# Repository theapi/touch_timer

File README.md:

# touch_timer
Kitchen timer with a touch interface

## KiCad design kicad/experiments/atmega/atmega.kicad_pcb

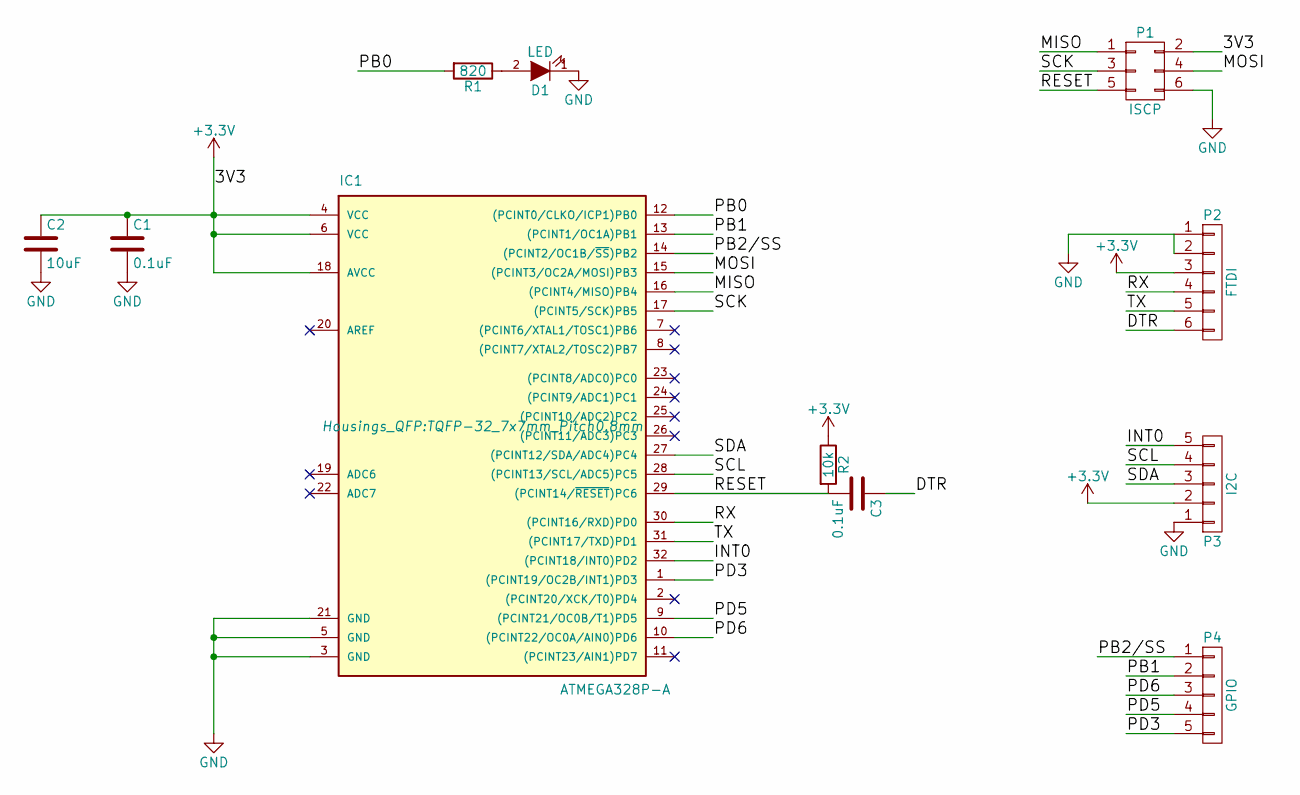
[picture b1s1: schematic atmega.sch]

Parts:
C1, C3: 0.1uF; C_0805_HandSoldering
C2: 10uF; C_0805_HandSoldering
D1: LED; LED_0805
IC1: ATMEGA328P-A; TQFP-32_7x7mm_Pitch0.8mm
P1: ISCP; Socket_Strip_Straight_2x03
P2: FTDI; Socket_Strip_Straight_1x06
P3: I2C; Pin_Header_Straight_1x05
P4: GPIO; Pin_Header_Straight_1x05
R1: 820; R_0805_HandSoldering
R2: 10k; R_0805_HandSoldering

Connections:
+3V3: C1.1, C2.1, IC1.4 (VCC), IC1.6 (VCC), IC1.18 (AVCC), P1.2, P2.3, P3.2, R2.1
/DTR: C3.1, P2.6
/INT0: IC1.32 ((PCINT18/INT0)PD2), P3.5
/MISO: IC1.16 ((PCINT4/MISO)PB4), P1.1
/MOSI: IC1.15 ((PCINT3/OC2A/MOSI)PB3), P1.4
/PB0: IC1.12 ((PCINT0/CLKO/ICP1)PB0), R1.2
/PB1: IC1.13 ((PCINT1/OC1A)PB1), P4.2
/PB2/SS: IC1.14 ((PCINT2/OC1B/~SS~)PB2), P4.1
/PD3: IC1.1 ((PCINT19/OC2B/INT1)PD3), P4.5
/PD5: IC1.9 ((PCINT21/OC0B/T1)PD5), P4.4
/PD6: IC1.10 ((PCINT22/OC0A/AIN0)PD6), P4.3
/RESET: C3.2, IC1.29 ((PCINT14/~RESET~)PC6), P1.5, R2.2
/RX: IC1.30 ((PCINT16/RXD)PD0), P2.4
/SCK: IC1.17 ((PCINT5/SCK)PB5), P1.3
/SCL: IC1.28 ((PCINT13/SCL/ADC5)PC5), P3.4
/SDA: IC1.27 ((PCINT12/SDA/ADC4)PC4), P3.3
/TX: IC1.31 ((PCINT17/TXD)PD1), P2.5
GND: C1.2, C2.2, D1.1 (K), IC1.3 (GND), IC1.5 (GND), IC1.21 (GND), P1.6, P2.1, P2.2, P3.1
unnamed: D1.2 (A), R1.1

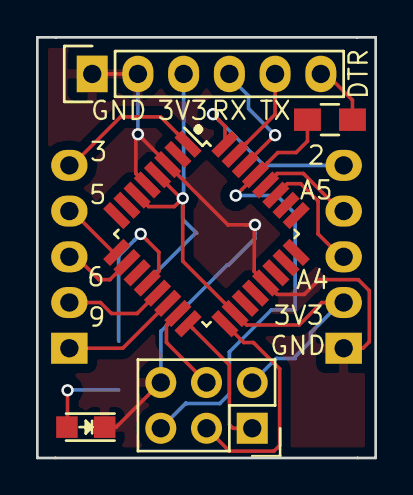
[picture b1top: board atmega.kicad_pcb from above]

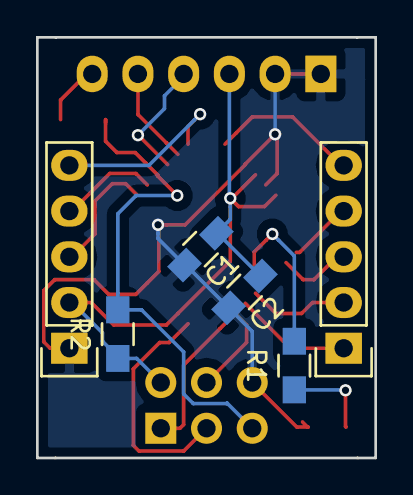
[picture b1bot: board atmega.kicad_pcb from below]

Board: 2 copper layers, 18.8 x 23.4 mm, 11 parts (6 on the bottom side), 19 nets.

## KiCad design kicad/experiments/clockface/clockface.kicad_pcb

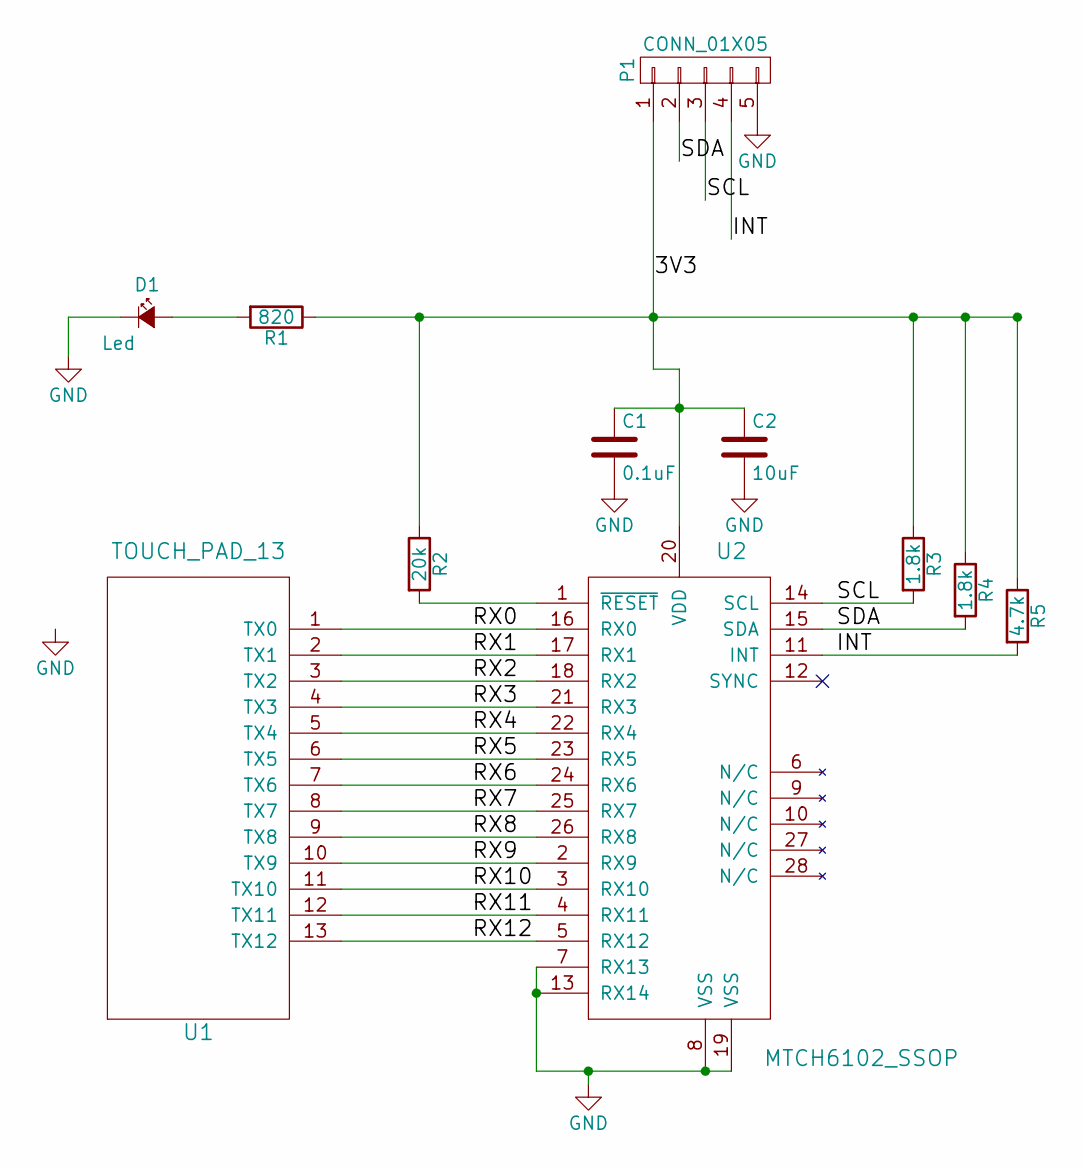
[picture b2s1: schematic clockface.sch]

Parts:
C1: 0.1uF; C_0805_HandSoldering
C2: 10uF; C_0805_HandSoldering
D1: Led; LED_0805
P1: CONN_01X05; SMD_Header_Straight_1x05
R1: 820; R_0805_HandSoldering
R2: 20k; R_0805_HandSoldering
R3, R4: 1.8k; R_0805_HandSoldering
R5: 4.7k; R_0805_HandSoldering
U1: TOUCH_PAD_13; CPA_12
U2: MTCH6102_SSOP; SSOP-28_5.3x10.2mm_Pitch0.65mm_masked

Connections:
/3V3: C1.1, C2.1, P1.1, R1.1, R2.1, R3.1, R4.1, R5.1, U2.20 (VDD)
/INT: P1.4, R5.2, U2.11 (INT)
/RX0: U1.1 (TX0), U2.16 (RX0)
/RX1: U1.2 (TX1), U2.17 (RX1)
/RX2: U1.3 (TX2), U2.18 (RX2)
/RX3: U1.4 (TX3), U2.21 (RX3)
/RX4: U1.5 (TX4), U2.22 (RX4)
/RX5: U1.6 (TX5), U2.23 (RX5)
/RX6: U1.7 (TX6), U2.24 (RX6)
/RX7: U1.8 (TX7), U2.25 (RX7)
/RX8: U1.9 (TX8), U2.26 (RX8)
/RX9: U1.10 (TX9), U2.2 (RX9)
/RX10: U1.11 (TX10), U2.3 (RX10)
/RX11: U1.12 (TX11), U2.4 (RX11)
/RX12: U1.13 (TX12), U2.5 (RX12)
/SCL: P1.3, R3.2, U2.14 (SCL)
/SDA: P1.2, R4.2, U2.15 (SDA)
GND: C1.2, C2.2, D1.1 (K), P1.5, U1.14, U2.7 (RX13), U2.8 (VSS), U2.13 (RX14), U2.19 (VSS)
unnamed: D1.2 (A), R1.2
unnamed: R2.2, U2.1 (~RESET)

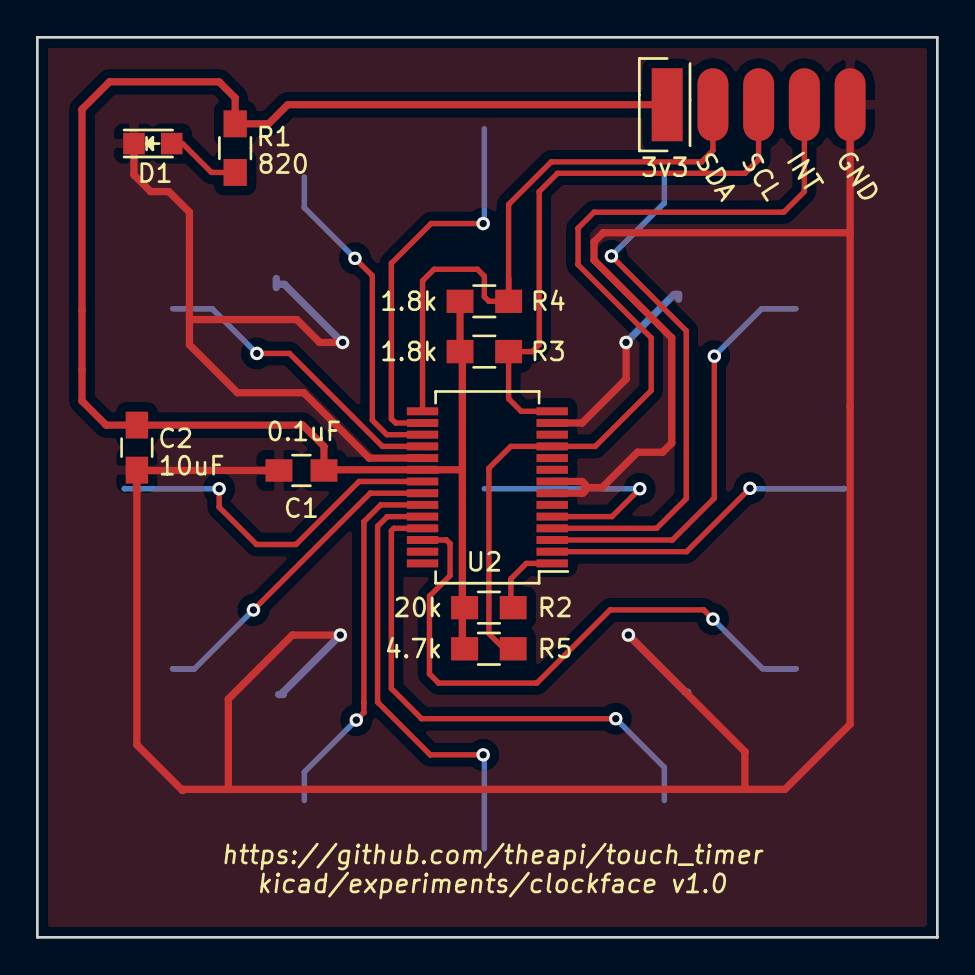
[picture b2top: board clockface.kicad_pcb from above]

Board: 2 copper layers, 50.0 x 50.0 mm, 11 parts (1 on the bottom side), 20 nets.

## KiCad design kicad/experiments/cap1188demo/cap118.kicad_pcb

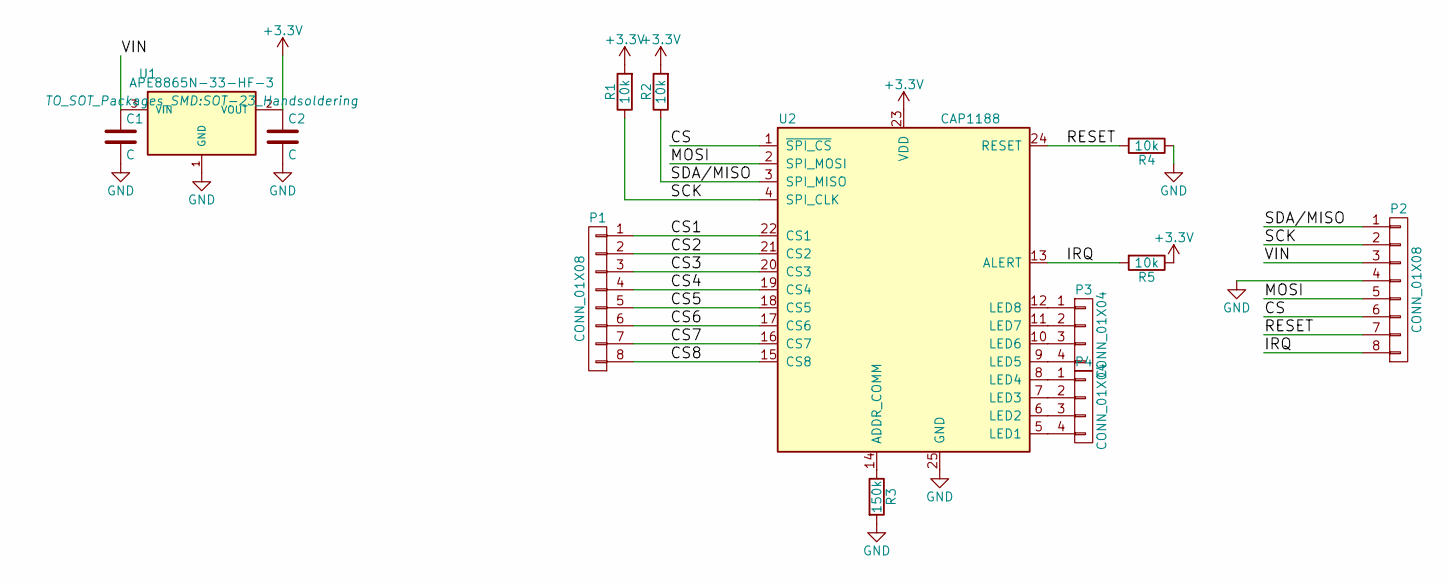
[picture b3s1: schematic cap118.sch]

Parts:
C1, C2: C; C_0805_HandSoldering
P1, P2: CONN_01X08; Pin_Header_Straight_1x08
P3, P4: CONN_01X04; Pin_Header_Straight_1x04
R1, R2, R4, R5: 10k; R_0805_HandSoldering
R3: 150k; R_0805_HandSoldering
U1: APE8865N-33-HF-3; SOT-23_Handsoldering
U2: CAP1188; QFN-24-1EP_4x4mm_Pitch0.5mm

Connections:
+3V3: C2.1, R1.2, R2.2, R5.1, U1.2 (VOUT), U2.23 (VDD)
/CS: P2.6, U2.1 (~SPI_CS)
/CS1: P1.1, U2.22 (CS1)
/CS2: P1.2, U2.21 (CS2)
/CS3: P1.3, U2.20 (CS3)
/CS4: P1.4, U2.19 (CS4)
/CS5: P1.5, U2.18 (CS5)
/CS6: P1.6, U2.17 (CS6)
/CS7: P1.7, U2.16 (CS7)
/CS8: P1.8, U2.15 (CS8)
/IRQ: P2.8, R5.2, U2.13 (ALERT)
/MOSI: P2.5, U2.2 (SPI_MOSI)
/RESET: P2.7, R4.2, U2.24 (RESET)
/SCK: P2.2, R1.1, U2.4 (SPI_CLK)
/SDA/MISO: P2.1, R2.1, U2.3 (SPI_MISO)
/VIN: C1.1, P2.3, U1.3 (VIN)
GND: C1.2, C2.2, P2.4, R3.2, R4.1, U1.1 (GND), U2.25 (GND)
unnamed: P3.1, U2.12 (LED8)
unnamed: P3.2, U2.11 (LED7)
unnamed: P3.3, U2.10 (LED6)
unnamed: P3.4, U2.9 (LED5)
unnamed: P4.1, U2.8 (LED4)
unnamed: P4.2, U2.7 (LED3)
unnamed: P4.3, U2.6 (LED2)
unnamed: P4.4, U2.5 (LED1)
unnamed: R3.1, U2.14 (ADDR_COMM)

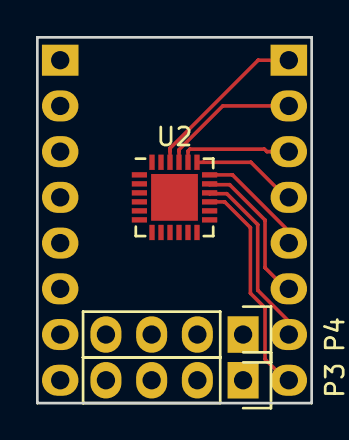
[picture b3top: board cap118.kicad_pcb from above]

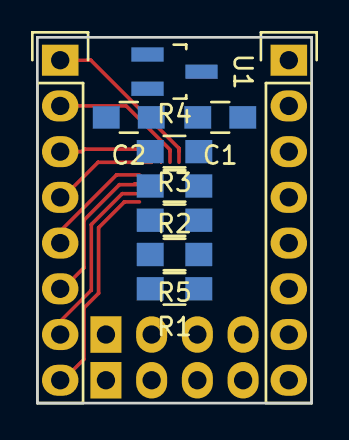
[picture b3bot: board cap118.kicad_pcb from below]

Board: 2 copper layers, 15.2 x 20.3 mm, 13 parts (10 on the bottom side), 26 nets.

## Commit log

2016-04-04 MTCH6102 schematic component
2016-04-04 Touch sensor datasheet
2016-04-04 ignore nothing
2016-04-05 Project library
2016-04-05 Initial footprint
2016-04-05 Clock like input
2016-04-06 Caps & resistors on the touch ic
2016-04-06 Layout (wip)
2016-04-06 Sqeeze it in
2016-04-06 APA_102C
2016-04-06 More squeezing
2016-04-07 Moved to sub folder
2016-04-07 Experiments
2016-04-07 RX traces
2016-04-07 Layed out
2016-04-07 Numbers on the keys
2016-04-08 Moved header closer to the edge
2016-04-09 Changed layout
2016-04-10 Vias not holes in the touch footprint
2016-04-11 tweaks
2016-04-11 gerbers
2016-04-11 Soldermask on the ic footprint
2016-04-12 Moved ground vias
2016-04-12 Wider VCC track
2016-04-12 via tweak
2016-04-13 Start of using clockface
2016-04-18 Renders & plot
2016-05-07 Start of CAP1188 experiment
2016-05-07 AT42QT1070-SSU
2016-05-09 Pin 1 marker
2016-05-09 Corrected SDA & SCL labels
2016-05-09 Flip layers
2016-05-09 Experimental atmega328p board
2016-05-09 Layout
2016-05-10 MTCH6102 proof of concept
2016-05-11 Start of the MTCH6102 library
2016-05-13 Through hole headers
2016-05-13 Silkscreen
